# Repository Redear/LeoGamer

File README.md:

LeoGamer
========

Arduino Leonardo based gaming system with joystick and MicroSD Card

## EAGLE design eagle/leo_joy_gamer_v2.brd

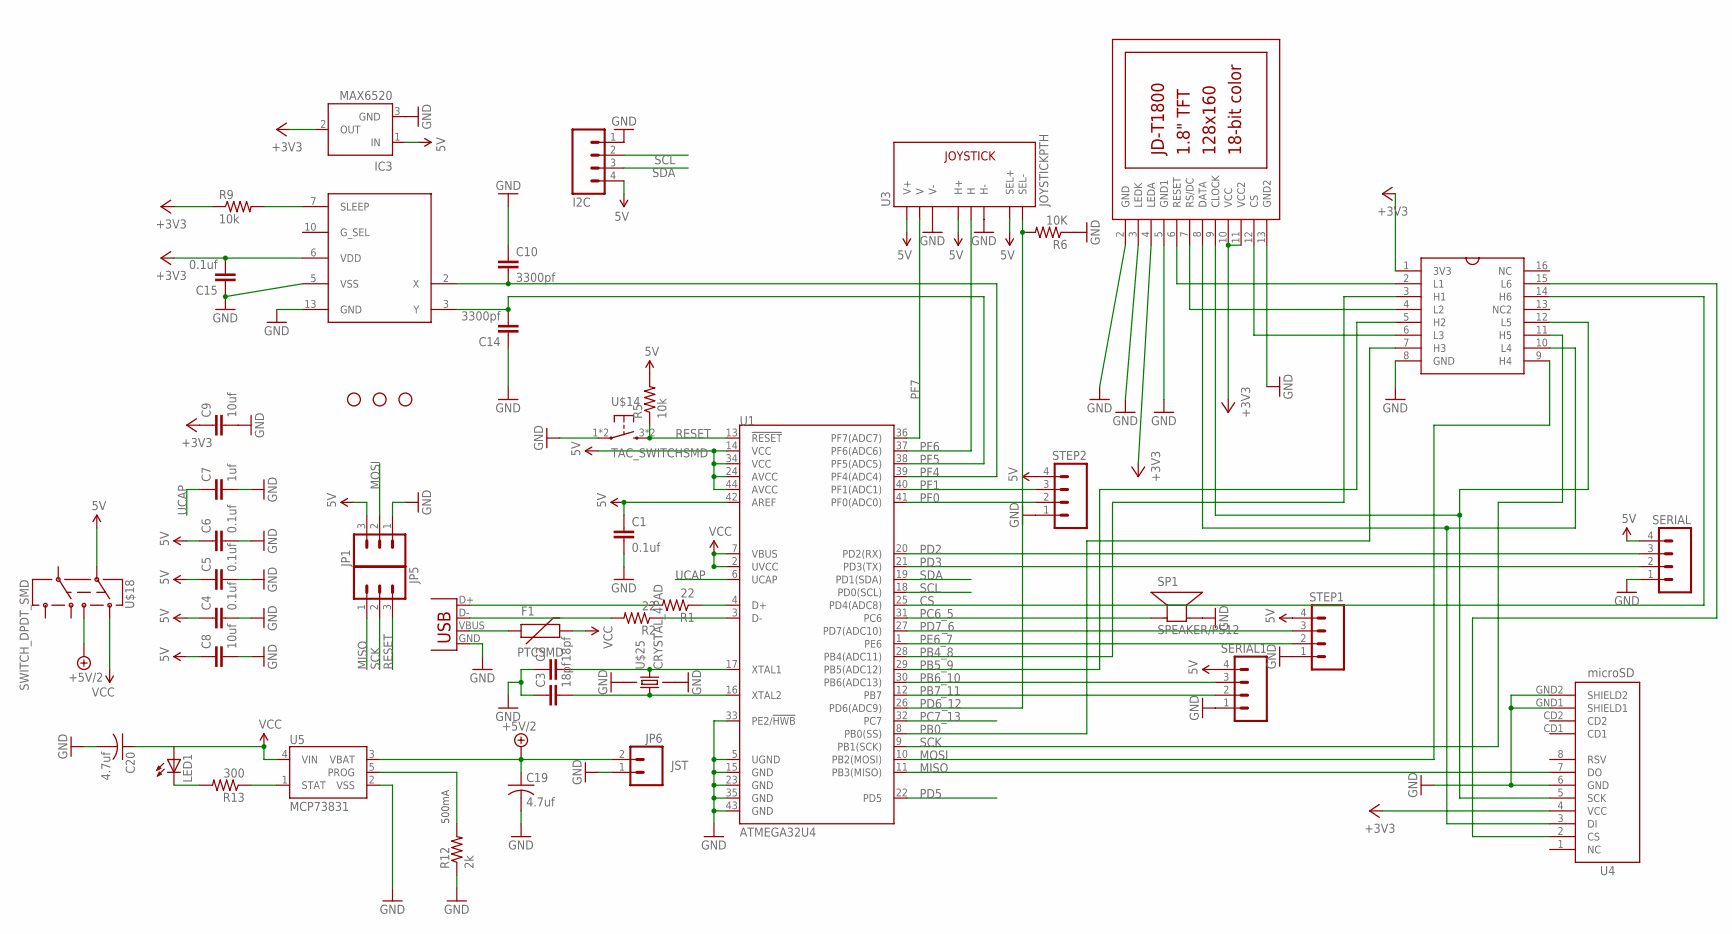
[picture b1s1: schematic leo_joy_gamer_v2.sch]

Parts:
C1, C4, C5, C6, C15: 0.1uf; 0805
C2, C3: 18pf; 0805
C7: 1uf; 0805
C8, C9: 10uf; 0805
C10, C14: 3300pf; 0805
C19, C20: 4.7uf; C0603
F1: PTCSMD; PTC-1206
I2C: M04LOCK; 1X04_LOCK
IC3: MAX6520; SOT23
JP1, JP5: M03LOCK; 1X03_LOCK
JP2, JP3, JP4: STAND-OFF
JP6: JST; JST-2-PTH
LCD1: JD-T1800
LED1: LEDCHIPLED_1206; CHIPLED_1206
R1, R2: 22; M0805
R5: 10k; M0805
R6: 10K; R0603
R9: 10k; R0805
R12: 2k; R0805
R13: 300; R0805
SERIAL, SERIAL1: M04LOCK; 1X04_LOCK
SP1: SPEAKER/PS12; PS12
STEP1, STEP2: M04LOCK; 1X04_LOCK
U1: ATMEGA32U4; QFN-44-NOPAD
U3: JOYSTICKPTH; JOYSTICK
U4: microSD; MICRO-SD-SOCKET-PP
U5: MCP73831; SOT23-5
U$2: CD4050SO_16_MIDDLE; SO_16
U$12: ACCELEROMETER_MMA6331L; LGA14
U$14: TAC_SWITCHSMD; TAC_SWITCH_SMD
U$18: SWITCH_DPDT_SMD; SWITCH_DPDT
U$25: CRYSTAL_4PAD; CRYSTAL_4PAD_TINY
X1: USBSMD; USB-MINIB

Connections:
5V: C1.1, C4.1, C5.1, C6.1, C8.1, I2C.4, IC3.1 (IN), JP1.3, R5.2, SERIAL.4, SERIAL1.4, STEP1.4, STEP2.4, U1.14 (VCC), U1.24 (AVCC), U1.34 (VCC), U1.42 (AREF), U1.44 (AVCC), U3.B1A (SEL+), U3.H1 (H+), U3.V1 (V+), U$18.7 (2)
+3V3: C9.1, C15.2, IC3.2 (OUT), LCD1.4 (LEDA), LCD1.10 (VCC), LCD1.11 (VCC2), R9.1, U4.4 (VCC), U$2.1 (3V3), U$12.6 (VDD)
+5V/2: C19.1, JP6.2, U5.3 (VBAT), U$18.8 (3)
CS: U1.25 (PD4(ADC8)), U$2.14 (H6)
D+: R1.2, X1.D+
D-: R2.2, X1.D-
GND: C1.2, C2.1, C3.1, C4.2, C5.2, C6.2, C7.2, C8.2, C9.2, C10.1, C14.1, C15.1, C19.2, C20.2, I2C.1, IC3.3 (GND), JP1.1, JP6.1, LCD1.2 (GND), LCD1.3 (LEDK), LCD1.5 (GND1), LCD1.13 (GND2), R6.1, R12.1, SERIAL.1, SERIAL1.1, SP1.P$2 (-), STEP1.1, STEP2.1, U1.5 (UGND), U1.15 (GND), U1.23 (GND), U1.33 (PE2/!HWB), U1.35 (GND), U1.43 (GND), U3.H3 (H-), U3.V3 (V-), U4.6 (GND), U4.GND1 (SHIELD1), U4.GND2 (SHIELD2), U5.2 (VSS), U$2.8 (GND), U$12.5 (VSS), U$12.13 (GND), U$14.1, U$14.2 (1), U$25.2 (GND2), U$25.4 (GND4), X1.GND
MISO: JP5.1, U1.11 (PB3(MISO)), U4.7 (DO)
MOSI: JP1.2, U1.10 (PB2(MOSI)), U$2.9 (H4)
MOSI_3V3: LCD1.8 (DATA), U4.3 (DI), U$2.10 (L4)
unnamed: LCD1.6 (RESET), U$2.2 (L1)
unnamed: C2.2, U1.17 (XTAL1), U$25.3
unnamed: C3.2, U1.16 (XTAL2), U$25.1
unnamed: LCD1.7 (RS/DC), U$2.4 (L2)
unnamed: LCD1.12 (CS), U$2.6 (L3)
unnamed: R1.1, U1.4 (D+)
unnamed: U4.2 (CS), U$2.15 (L6)
unnamed: R2.1, U1.3 (D-)
unnamed: R9.2, U$12.7 (SLEEP)
unnamed: R13.1, U5.1 (STAT)
unnamed: LED1.C, R13.2
PB0: U1.8 (PB0(SS)), U$2.7 (H3)
PB4_8: U1.28 (PB4(ADC11)), U$2.3 (H1)
PB5_9: U1.29 (PB5(ADC12)), U$2.5 (H2)
PB6_10: SERIAL1.3, U1.30 (PB6(ADC13))
PB7_11: SERIAL1.2, U1.12 (PB7)
PC6_5: SP1.P$1 (+), U1.31 (PC6)
PC7_13: U1.32 (PC7)
PD2: SERIAL.3, U1.20 (PD2(RX))
PD3: SERIAL.2, U1.21 (PD3(TX))
PD5: U1.22 (PD5)
PD6_12: R6.2, U1.26 (PD6(ADC9)), U3.B2A (SEL-)
PD7_6: STEP1.3, U1.27 (PD7(ADC10))
PE6_7: STEP1.2, U1.1 (PE6)
PF0: STEP2.2, U1.41 (PF0(ADC0))
PF1: STEP2.3, U1.40 (PF1(ADC1))
PF4: C10.2, U1.39 (PF4(ADC4)), U$12.2 (X)
PF5: C14.2, U1.38 (PF5(ADC5)), U$12.3 (Y)
PF6: U1.37 (PF6(ADC6)), U3.H2 (H)
PF7: U1.36 (PF7(ADC7)), U3.V2 (V)
PROG: R12.2, U5.5 (PROG)
RESET: JP5.3, R5.1, U1.13 (!RESET), U$14.3, U$14.4 (3)
SCK: JP5.2, U1.9 (PB1(SCK)), U$2.11 (H5)
SCK_3V3: LCD1.9 (CLOCK), U4.5 (SCK), U$2.12 (L5)
SCL: I2C.2, U1.18 (PD0(SCL))
SDA: I2C.3, U1.19 (PD1(SDA))
UCAP: C7.1, U1.6 (UCAP)
VBUS: F1.1, X1.VBUS
VCC: C20.1, F1.2, LED1.A, U1.2 (UVCC), U1.7 (VBUS), U5.4 (VIN), U$18.1

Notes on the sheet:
500mA

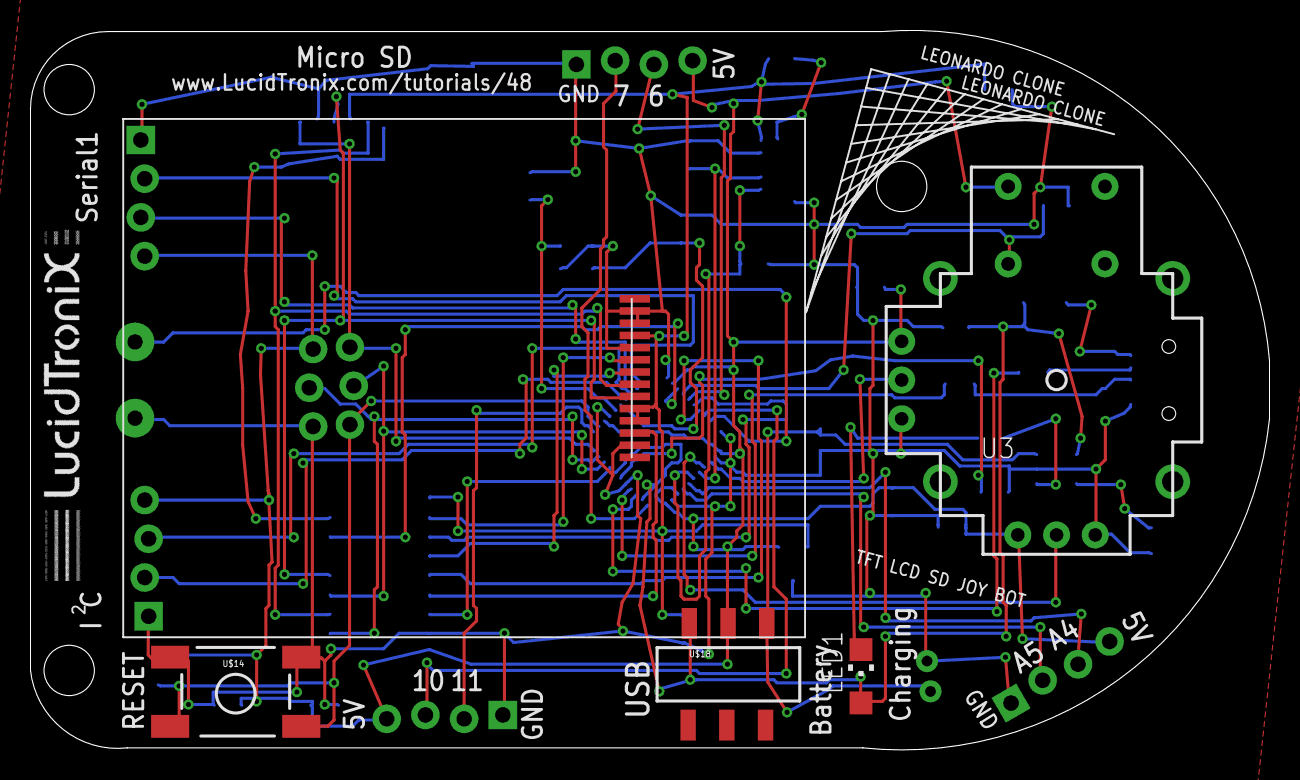
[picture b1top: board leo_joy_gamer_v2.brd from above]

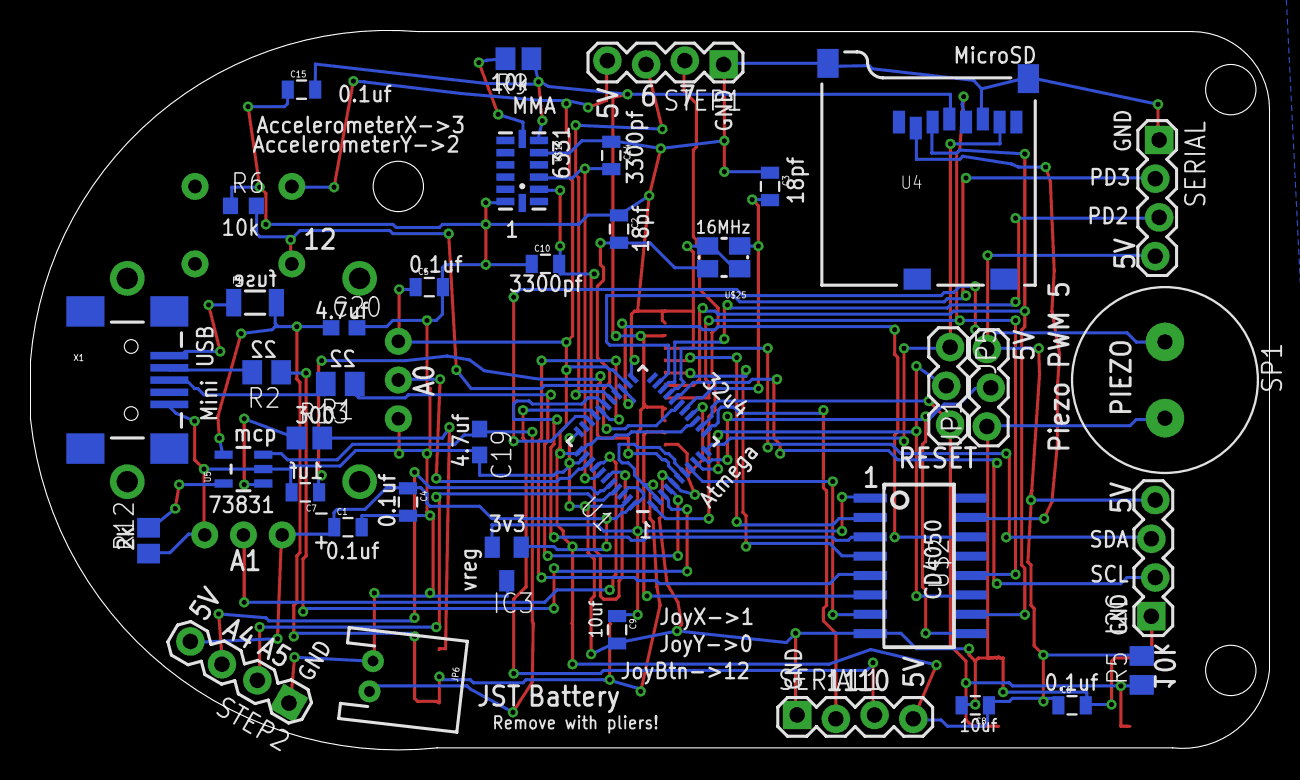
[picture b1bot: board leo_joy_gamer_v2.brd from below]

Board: 2 copper layers, 81.3 x 47.2 mm, 48 parts (39 on the bottom side), 47 nets.

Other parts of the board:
U$6: LUCIDTRONIX_LOGO_.75_INCH

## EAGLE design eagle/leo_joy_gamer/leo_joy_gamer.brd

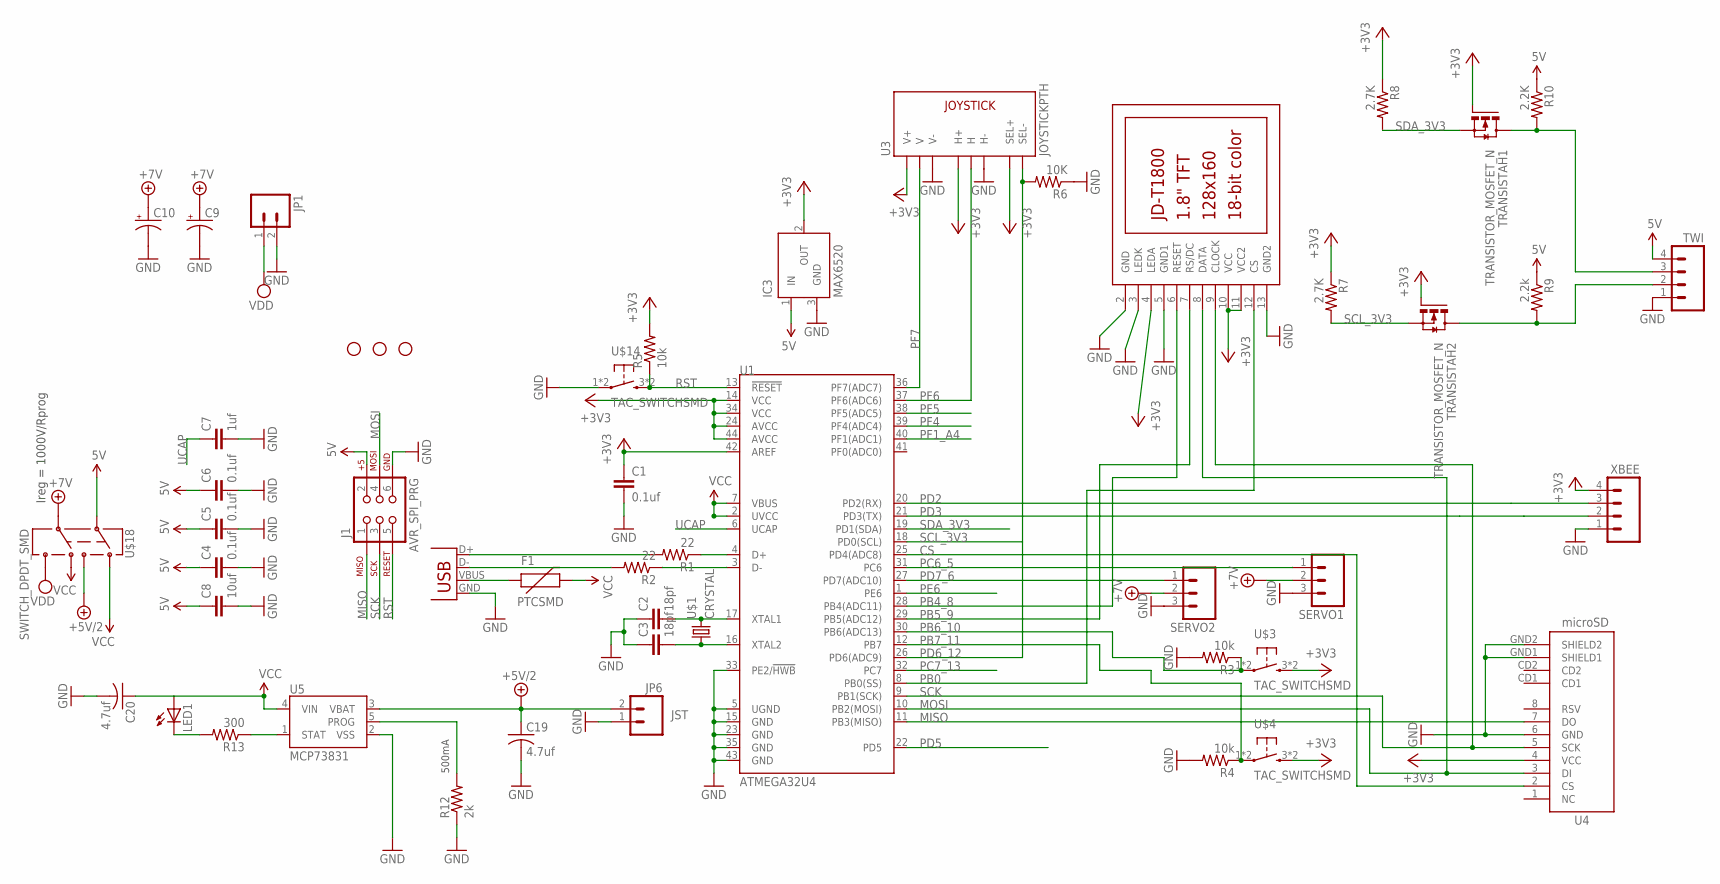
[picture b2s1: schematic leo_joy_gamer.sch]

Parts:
C1, C4, C5, C6: 0.1uf; 0805
C2, C3: 18pf; 0805
C7: 1uf; 0805
C8: 10uf; 0805
C9, C10: CPOL-USD; PANASONIC_D
C19, C20: 4.7uf; C0603
F1: PTCSMD; PTC-1206
IC3: MAX6520; SOT23
J1: AVR_SPI_PRG; 2X3
JP1: M02LOCK; 1X02_LOCK
JP2, JP3, JP4: STAND-OFF
JP6: JST; JST-2-PTH
LCD1: JD-T1800
LED1: LEDCHIPLED_1206; CHIPLED_1206
R1, R2: 22; M0805
R3, R4, R5: 10k; M0805
R6: 10K; R0603
R7, R8: 2.7K; M0805
R9: 2.2k; M0805
R10: 2.2K; M0805
R12: 2k; R0805
R13: 300; R0805
SERVO1, SERVO2: M03LOCK; 1X03_LOCK
TRANSISTAH1, TRANSISTAH2: TRANSISTOR_MOSFET_N; SOT23
TWI: M04LOCK; 1X04_LOCK
U1: ATMEGA32U4; QFN-44-NOPAD
U3: JOYSTICKPTH; JOYSTICK
U4: microSD; MICRO-SD-SOCKET-PP
U5: MCP73831; SOT23-5
U$1: CRYSTAL; CRYSTAL_SMD
U$3, U$4, U$14: TAC_SWITCHSMD; TAC_SWITCH_SMD
U$18: SWITCH_DPDT_SMD; SWITCH_DPDT
X2: USB-MICROB
XBEE: M04LOCK; 1X04_LOCK

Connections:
5V: C4.1, C5.1, C6.1, C8.1, IC3.1 (IN), J1.2, R9.1, R10.1, TWI.4, U$18.7 (2)
+3V3: C1.1, IC3.2 (OUT), LCD1.4 (LEDA), LCD1.10 (VCC), LCD1.11 (VCC2), R5.2, R7.1, R8.1, TRANSISTAH1.1 (G), TRANSISTAH2.1 (G), U1.14 (VCC), U1.24 (AVCC), U1.34 (VCC), U1.42 (AREF), U1.44 (AVCC), U3.B1A (SEL+), U3.H1 (H+), U3.V1 (V+), U4.4 (VCC), U$3.3, U$3.4 (3), U$4.3, U$4.4 (3), XBEE.4
+5V/2: C19.1, JP6.2, U5.3 (VBAT), U$18.8 (3)
+7V: C9.+, C10.+, SERVO1.2, SERVO2.2, U$18.10 (5)
CS: U1.25 (PD4(ADC8)), U4.2 (CS)
D+: R1.2, X2.D+
D-: R2.2, X2.D-
GND: C1.2, C2.1, C3.1, C4.2, C5.2, C6.2, C7.2, C8.2, C9.-, C10.-, C19.2, C20.2, IC3.3 (GND), J1.6, JP1.2, JP6.1, LCD1.2 (GND), LCD1.3 (LEDK), LCD1.5 (GND1), LCD1.13 (GND2), R3.2, R4.2, R6.1, R12.1, SERVO1.3, SERVO2.3, TWI.1, U1.5 (UGND), U1.15 (GND), U1.23 (GND), U1.33 (PE2/!HWB), U1.35 (GND), U1.43 (GND), U3.H3 (H-), U3.V3 (V-), U4.6 (GND), U4.GND1 (SHIELD1), U4.GND2 (SHIELD2), U5.2 (VSS), U$14.1, U$14.2 (1), X2.GND, XBEE.1
MISO: J1.1, U1.11 (PB3(MISO)), U4.7 (DO)
MOSI: J1.4, LCD1.8 (DATA), U1.10 (PB2(MOSI)), U4.3 (DI)
unnamed: C2.2, U1.17 (XTAL1), U$1.2
unnamed: C3.2, U1.16 (XTAL2), U$1.1
unnamed: R1.1, U1.4 (D+)
unnamed: R2.1, U1.3 (D-)
unnamed: R13.1, U5.1 (STAT)
unnamed: LED1.C, R13.2
PB0: LCD1.12 (CS), U1.8 (PB0(SS))
PB4_8: LCD1.6 (RESET), U1.28 (PB4(ADC11))
PB5_9: LCD1.7 (RS/DC), U1.29 (PB5(ADC12))
PB6_10: R3.1, U1.30 (PB6(ADC13)), U$3.1, U$3.2 (1)
PB7_11: R4.1, U1.12 (PB7), U$4.1, U$4.2 (1)
PC6_5: SERVO1.1, U1.31 (PC6)
PC7_13: U1.32 (PC7)
PD2: U1.20 (PD2(RX)), XBEE.3
PD3: U1.21 (PD3(TX)), XBEE.2
PD5: U1.22 (PD5)
PD6_12: R6.2, U1.26 (PD6(ADC9)), U3.B2A (SEL-)
PD7_6: SERVO2.1, U1.27 (PD7(ADC10))
PE6: U1.1 (PE6)
PF1_A4: U1.40 (PF1(ADC1))
PF4: U1.39 (PF4(ADC4))
PF5: U1.38 (PF5(ADC5))
PF6: U1.37 (PF6(ADC6)), U3.H2 (H)
PF7: U1.36 (PF7(ADC7)), U3.V2 (V)
PROG: R12.2, U5.5 (PROG)
RST: J1.5, R5.1, U1.13 (!RESET), U$14.3, U$14.4 (3)
SCK: J1.3, LCD1.9 (CLOCK), U1.9 (PB1(SCK)), U4.5 (SCK)
SCL: R9.2, TRANSISTAH2.3 (D), TWI.2
SCL_3V3: R7.2, TRANSISTAH2.2 (S), U1.18 (PD0(SCL))
SDA: R10.2, TRANSISTAH1.3 (D), TWI.3
SDA_3V3: R8.2, TRANSISTAH1.2 (S), U1.19 (PD1(SDA))
UCAP: C7.1, U1.6 (UCAP)
VBUS: F1.1, X2.VBUS
VCC: C20.1, F1.2, LED1.A, U1.2 (UVCC), U1.7 (VBUS), U5.4 (VIN), U$18.1, U$18.9 (4)
VDD: JP1.1, U$18.11 (6)

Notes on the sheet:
500mA
Ireg = 1000V/Rprog

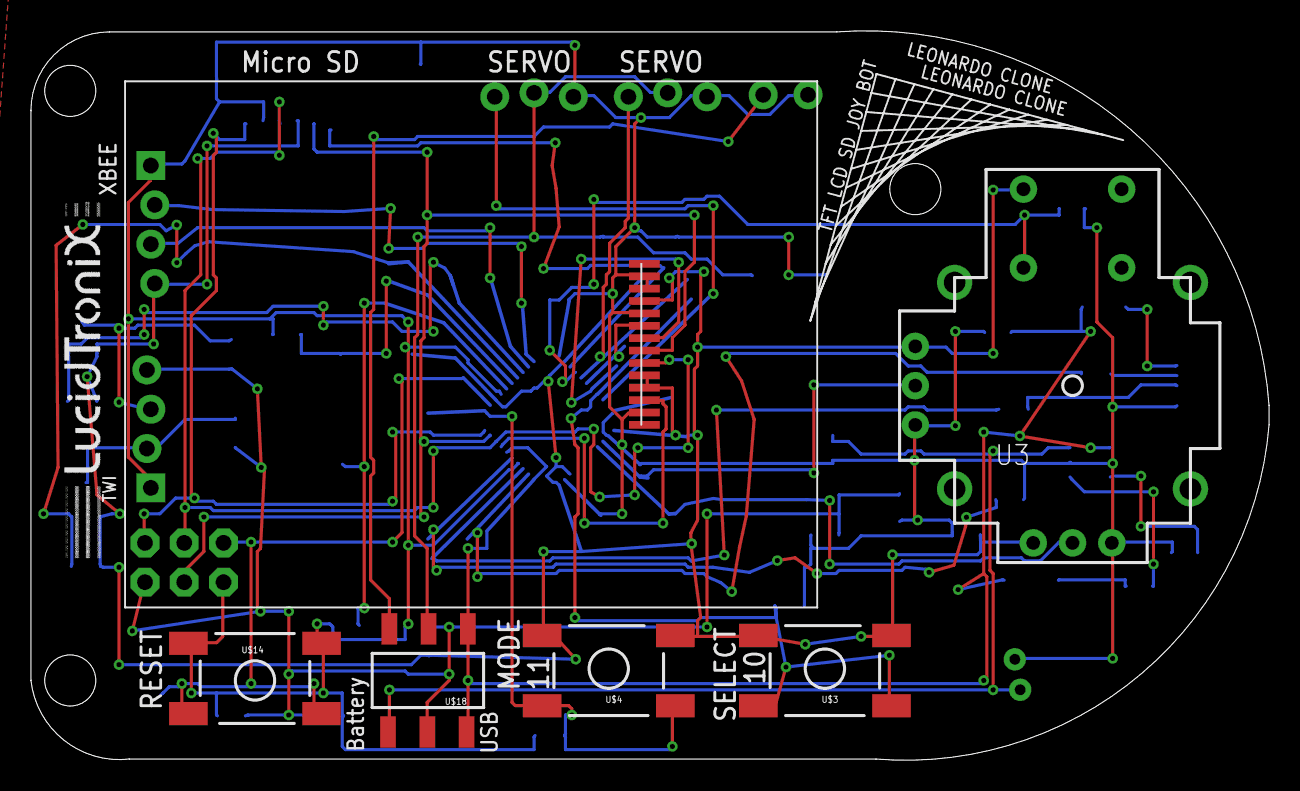
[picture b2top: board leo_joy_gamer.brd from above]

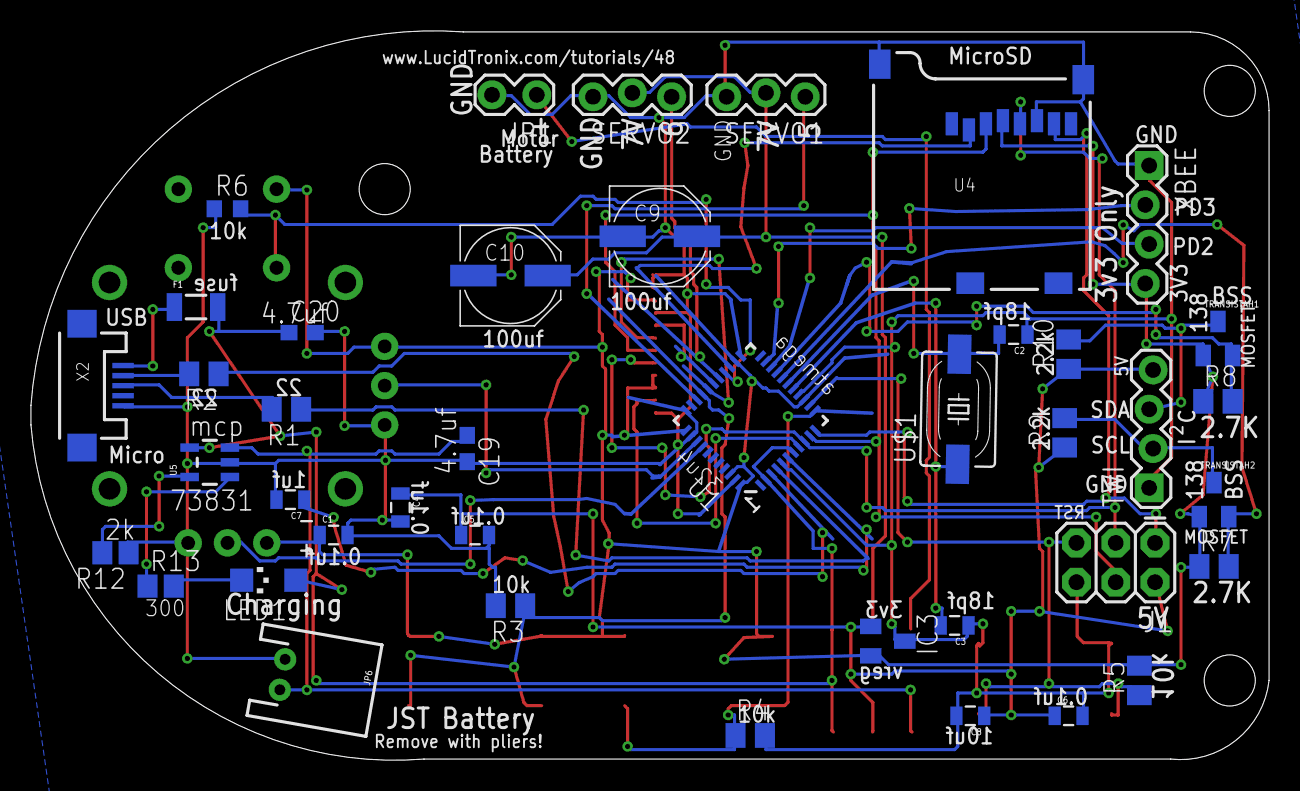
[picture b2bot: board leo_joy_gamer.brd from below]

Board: 2 copper layers, 80.0 x 47.1 mm, 51 parts (41 on the bottom side), 39 nets.

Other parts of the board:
U$6: LUCIDTRONIX_LOGO_.75_INCH

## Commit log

2013-08-01 arduino files added
2013-08-01 added eagle files
2013-08-02 small 1st change to repo
2013-08-02 Added lucidBounce the soon to be improved file
2013-08-07 Modified lucidBounce for cleaner play
2013-08-14 add some pics and beautified the bounce
2013-09-03 added pics for tutorial and stubs for meteorAttack
2013-09-03 changed name to meteorAttack
2013-09-07 Began meteorAttack
2013-09-09 Put in explosion and collision detection
2013-09-10 added meshes and eagle CAD
2013-09-13 added attack lines
2013-09-13 added keyboard
2013-09-14 accelerometer mouse
2013-09-14 finally got meteors to disappear
2013-09-14 added leo gamer mesh 2
